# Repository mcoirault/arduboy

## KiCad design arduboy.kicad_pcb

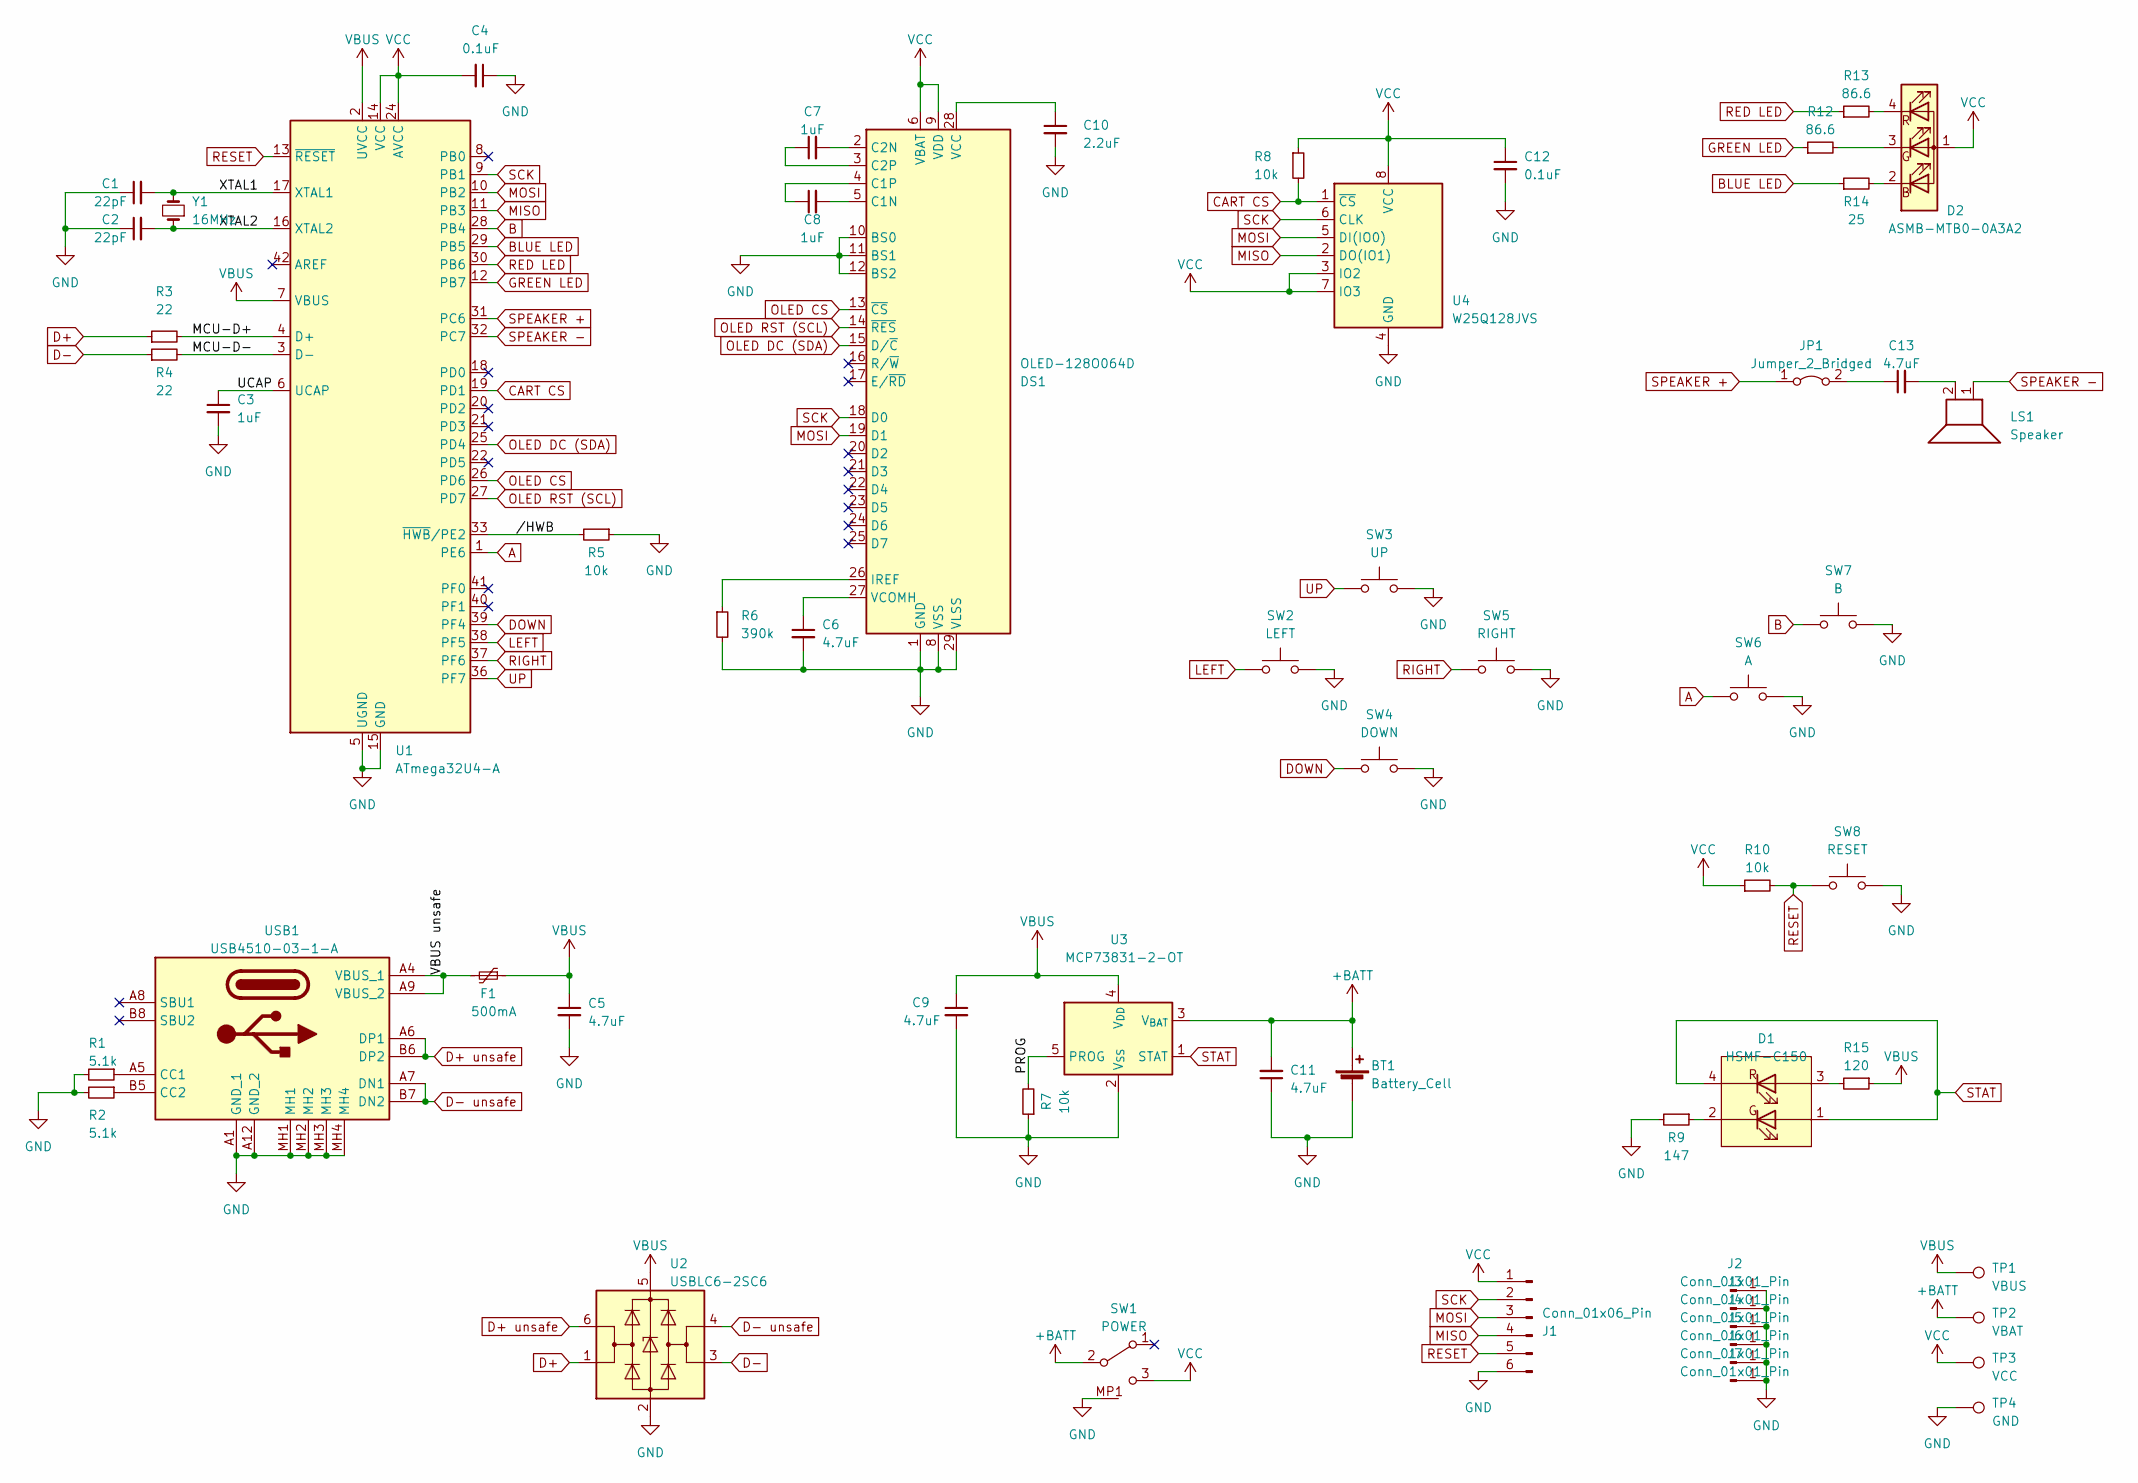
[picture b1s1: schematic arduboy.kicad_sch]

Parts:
BT1: Battery_Cell; JST_SH_SM02B-SRSS-TB_1x02-1MP_P1.00mm_Horizontal
C1, C2: 22pF; C_1206_3216Metric_Pad1.33x1.80mm_HandSolder ref under the c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; Manufacturer_Part_Number VJ1206A220JXQPW1BC; Mouser Part Number 77-VJ1206A220JXQPBC
C3, C7, C8: 1uF; C_1206_3216Metric_Pad1.33x1.80mm_HandSolder ref under the c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; Manufacturer_Part_Number 1206B105J500CT; Mouser Part Number 791-1206B105J500CT
C4, C12: 0.1uF; C_1206_3216Metric_Pad1.33x1.80mm_HandSolder ref under the c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; Manufacturer_Part_Number GRM3195C1H104JA05D; Mouser Part Number 81-GRM3195C1H104JA5D
C5, C6, C9, C11, C13: 4.7uF; C_1206_3216Metric_Pad1.33x1.80mm_HandSolder ref under the c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; Manufacturer_Part_Number GRM31CR71H475KA12K; Mouser Part Number 81-GRM31CR71H475KA2K
C10: 2.2uF; C_1206_3216Metric_Pad1.33x1.80mm_HandSolder ref under the c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; Manufacturer_Part_Number CL31B225KBHNFNE; Mouser Part Number 187-CL31B225KBHNFNE
D1: HSMF-C150; HSMFC150; Mouser Part Number 630-HSMF-C150
D2: ASMB-MTB0-0A3A2; LED_Avago_PLCC4_3.2x2.8mm_CW; Manufacturer_Part_Number ASMB-MTB0-0B3A2; Mouser Part Number 630-ASMB-MTB0-0B3A2
DS1: OLED-128O064D; OLED_30pins_0.7mm
F1: 500mA; polyfuse_5.1mm; Manufacturer_Part_Number MF-R050; Mouser Part Number 652-MFR050
J1: Conn_01x06_Pin; custom ISP header; Manufacturer_Part_Number M22-2530605; Mouser Part Number 855-M22-2530605
J2, J3, J4, J5, J6, J7: Conn_01x01_Pin; MountingHole_2.2mm_M2_Pad
JP1: Jumper_2_Bridged; Jumper for SMD 1206 bridged
LS1: Speaker; Buzzer_Mallory_AST1109MLTRQ; Manufacturer_Part_Number AST1109MLTRQ; Mouser Part Number 539-AST1109MLTRQ
R1, R2: 5.1k; R_1206_3216Metric_Pad1.30x1.75mm_HandSolder with ref under 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; Manufacturer_Part_Number RMCF1206FT5K10; Mouser Part Number 708-RMCF1206FT5K10
R3, R4: 22; R_1206_3216Metric_Pad1.30x1.75mm_HandSolder with ref under 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; Manufacturer_Part_Number CR1206-FX-22R0ELF; Mouser Part Number 652-CR1206FX-22R0ELF
R5, R7, R8, R10: 10k; R_1206_3216Metric_Pad1.30x1.75mm_HandSolder with ref under 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; Manufacturer_Part_Number RNCP1206FTD10K0; Mouser Part Number 708-RNCP1206FTD10K0
R6: 390k; R_1206_3216Metric_Pad1.30x1.75mm_HandSolder with ref under 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; Manufacturer_Part_Number ESR18EZPF3903; Mouser Part Number 755-ESR18EZPF3903
R9: 147; R_1206_3216Metric_Pad1.30x1.75mm_HandSolder with ref under 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; Manufacturer_Part_Number CR1206-FX-1470ELF; Mouser Part Number 652-CR1206FX-1470ELF
R12, R13: 86.6; R_1206_3216Metric_Pad1.30x1.75mm_HandSolder with ref under 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; Mouser Part Number 660-RK73H2BTTD86R6F
R14: 25; R_1206_3216Metric_Pad1.30x1.75mm_HandSolder with ref under 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; Mouser Part Number 660-RK73H2BTTD25R5F
R15: 120; R_1206_3216Metric_Pad1.30x1.75mm_HandSolder with ref under 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; Manufacturer_Part_Number CR1206-FX-1200ELF; Mouser Part Number 652-CR1206FX-1200ELF
SW1: POWER; PCM12SMTR; Manufacturer_Part_Number PCM12SMTR; Mouser Part Number 611-PCM12SMTR
SW2: LEFT; TS18525SL260SMTTR; Manufacturer_Part_Number TS18-5-15-SL-160-SMT-TR; Mouser Part Number 179-TS18515SL160SMTT
SW3: UP; TS18525SL260SMTTR; Manufacturer_Part_Number TS18-5-15-SL-160-SMT-TR; Mouser Part Number 179-TS18515SL160SMTT
SW4: DOWN; TS18525SL260SMTTR; Manufacturer_Part_Number TS18-5-15-SL-160-SMT-TR; Mouser Part Number 179-TS18515SL160SMTT
SW5: RIGHT; TS18525SL260SMTTR; Manufacturer_Part_Number TS18-5-15-SL-160-SMT-TR; Mouser Part Number 179-TS18515SL160SMTT
SW6: A; TS18525SL260SMTTR; Manufacturer_Part_Number TS18-5-25-SL-260-SMT-TR; Mouser Part Number 179-TS18525SL260SMTT
SW7: B; TS18525SL260SMTTR; Manufacturer_Part_Number TS18-5-25-SL-260-SMT-TR; Mouser Part Number 179-TS18525SL260SMTT
SW8: RESET; 436353045816; Manufacturer_Part_Number 436353045816; Mouser Part Number 710-436353045816
TP1: VBUS; TestPoint_Pad_D2.0mm
TP2: VBAT; TestPoint_Pad_D2.0mm
TP3: VCC; TestPoint_Pad_D2.0mm
TP4: GND; TestPoint_Pad_D2.0mm
U1: ATmega32U4-A; TQFP-44_10x10mm_P0.8mm; Manufacturer_Part_Number ATMEGA32U4-AU; Mouser Part Number 556-ATMEGA32U4-AU
U2: USBLC6-2SC6; SOT-23-6 with dot marker; Manufacturer_Part_Number USBLC6-2SC6; Mouser Part Number 511-USBLC6-2SC6
U3: MCP73831-2-OT; SOT-23-5 with dot marker; Manufacturer_Part_Number MCP73831T-2DCI/OT; Mouser Part Number 579-MCP73831T-2DCIOT
U4: W25Q128JVS; SOIC-8_5.275x5.275mm_P1.27mm; Manufacturer_Part_Number W25Q128JVSIQ TR; Mouser Part Number 454-W25Q128JVSIQTR
USB1: USB4510-03-1-A; USB4510031A; Mouser Part Number 640-USB4510031A
Y1: 16MHz; Crystal_HC46-X_Vertical; Manufacturer_Part_Number ECS-160-20-46X; Mouser Part Number 520-160-20-46X

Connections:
+BATT: BT1.1 (+), C11.2, SW1.2 (B), TP2.1, U3.3 (V_{BAT})
/MCU-D+: R3.2, U1.4 (D+)
/MCU-D-: R4.2, U1.3 (D-)
/PROG: R7.2, U3.5 (PROG)
/UCAP: C3.1, U1.6 (UCAP)
/VBUS unsafe: F1.2, USB1.A4 (VBUS_1), USB1.A9 (VBUS_2)
/XTAL1: C1.2, U1.17 (XTAL1), Y1.2
/XTAL2: C2.2, U1.16 (XTAL2), Y1.1
//HWB: R5.2, U1.33 (~HWB/PE2)
A: SW6.1, SW6.2, U1.1 (PE6)
B: SW7.1, SW7.2, U1.28 (PB4)
BLUE LED: R14.1, U1.29 (PB5)
CART CS: R8.2, U1.19 (PD1), U4.1 (~CS)
D+: R3.1, U2.1 (I/O1)
D+ unsafe: U2.6 (I/O1), USB1.A6 (DP1), USB1.B6 (DP2)
D-: R4.1, U2.3 (I/O2)
D- unsafe: U2.4 (I/O2), USB1.A7 (DN1), USB1.B7 (DN2)
DOWN: SW4.1, SW4.2, U1.39 (PF4)
GND: BT1.2 (-), BT1.MP, C1.1, C2.1, C3.2, C4.1, C5.2, C6.2, C9.2, C10.2, C11.1, C12.2, DS1.1 (GND), DS1.8 (VSS), DS1.10 (BS0), DS1.11 (BS1), DS1.12 (BS2), DS1.29 (VLSS), DS1.30 (GND), J1.6, J2.1, J3.1, J4.1, J5.1, J6.1, J7.1, R1.2, R2.2, R5.1, R6.2, R7.1, R9.2, SW1.MP1, SW1.MP2, SW1.MP3, SW1.MP4, SW2.3, SW2.4, SW3.3, SW3.4, SW4.3, SW4.4, SW5.3, SW5.4, SW6.3, SW6.4, SW7.3, SW7.4, SW8.2, SW8.4, TP4.1, U1.5 (UGND), U1.15 (GND), U1.23 (GND), U1.35 (GND), U1.43 (GND), U2.2 (GND), U3.2 (V_{SS}), U4.4 (GND), USB1.A1 (GND_1), USB1.A12 (GND_2), USB1.MH1, USB1.MH2, USB1.MH3, USB1.MH4
GREEN LED: R12.1, U1.12 (PB7)
LEFT: SW2.1, SW2.2, U1.38 (PF5)
MISO: J1.4, U1.11 (PB3), U4.2 (DO(IO1))
MOSI: DS1.19 (D1), J1.3, U1.10 (PB2), U4.5 (DI(IO0))
unnamed: C13.2, LS1.2
unnamed: D1.2 (GC), R9.1
unnamed: D1.3 (RA), R15.2
unnamed: D2.2 (BK), R14.2
unnamed: D2.3 (GK), R12.2
unnamed: D2.4 (RK), R13.2
unnamed: C8.2, DS1.5 (C1N)
unnamed: C8.1, DS1.4 (C1P)
unnamed: C7.2, DS1.2 (C2N)
unnamed: C7.1, DS1.3 (C2P)
unnamed: DS1.26 (IREF), R6.1
unnamed: C10.1, DS1.28 (VCC)
unnamed: C6.1, DS1.27 (VCOMH)
unnamed: C13.1, JP1.2 (B)
unnamed: R1.1, USB1.A5 (CC1)
unnamed: R2.1, USB1.B5 (CC2)
OLED CS: DS1.13 (~CS), U1.26 (PD6)
OLED DC (SDA): DS1.15 (D/~C), U1.25 (PD4)
OLED RST (SCL): DS1.14 (~RES), U1.27 (PD7)
RED LED: R13.1, U1.30 (PB6)
RESET: J1.5, R10.2, SW8.1, SW8.3, U1.13 (~RESET)
RIGHT: SW5.1, SW5.2, U1.37 (PF6)
SCK: DS1.18 (D0), J1.2, U1.9 (PB1), U4.6 (CLK)
SPEAKER +: JP1.1 (A), U1.31 (PC6)
SPEAKER -: LS1.1, U1.32 (PC7)
STAT: D1.1 (GA), D1.4 (RC), U3.1 (STAT)
UP: SW3.1, SW3.2, U1.36 (PF7)
VBUS: C5.1, C9.1, F1.1, R15.1, TP1.1, U1.2 (UVCC), U1.7 (VBUS), U2.5 (VBUS), U3.4 (V_{DD})
VCC: C4.2, C12.1, D2.1 (A), DS1.6 (VBAT), DS1.9 (VDD), J1.1, R8.1, R10.1, SW1.3 (C), TP3.1, U1.14 (VCC), U1.24 (AVCC), U1.34 (VCC), U1.44 (AVCC), U4.3 (IO2), U4.7 (IO3), U4.8 (VCC)

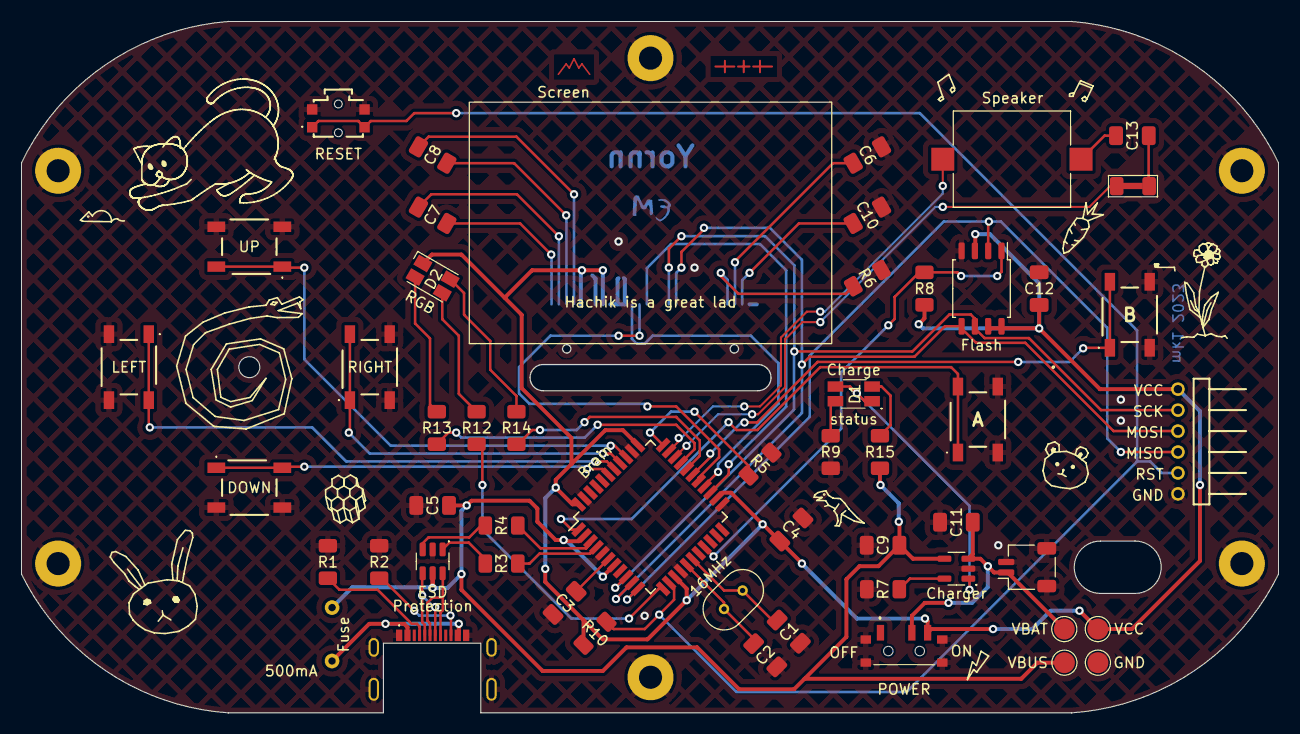
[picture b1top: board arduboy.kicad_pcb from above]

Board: 2 copper layers, 120.0 x 66.0 mm, 59 parts (1 on the bottom side), 52 nets.

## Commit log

2023-04-20 Add back silkscreen
2023-04-20 Fix footprints to use 1210 according to selected components
